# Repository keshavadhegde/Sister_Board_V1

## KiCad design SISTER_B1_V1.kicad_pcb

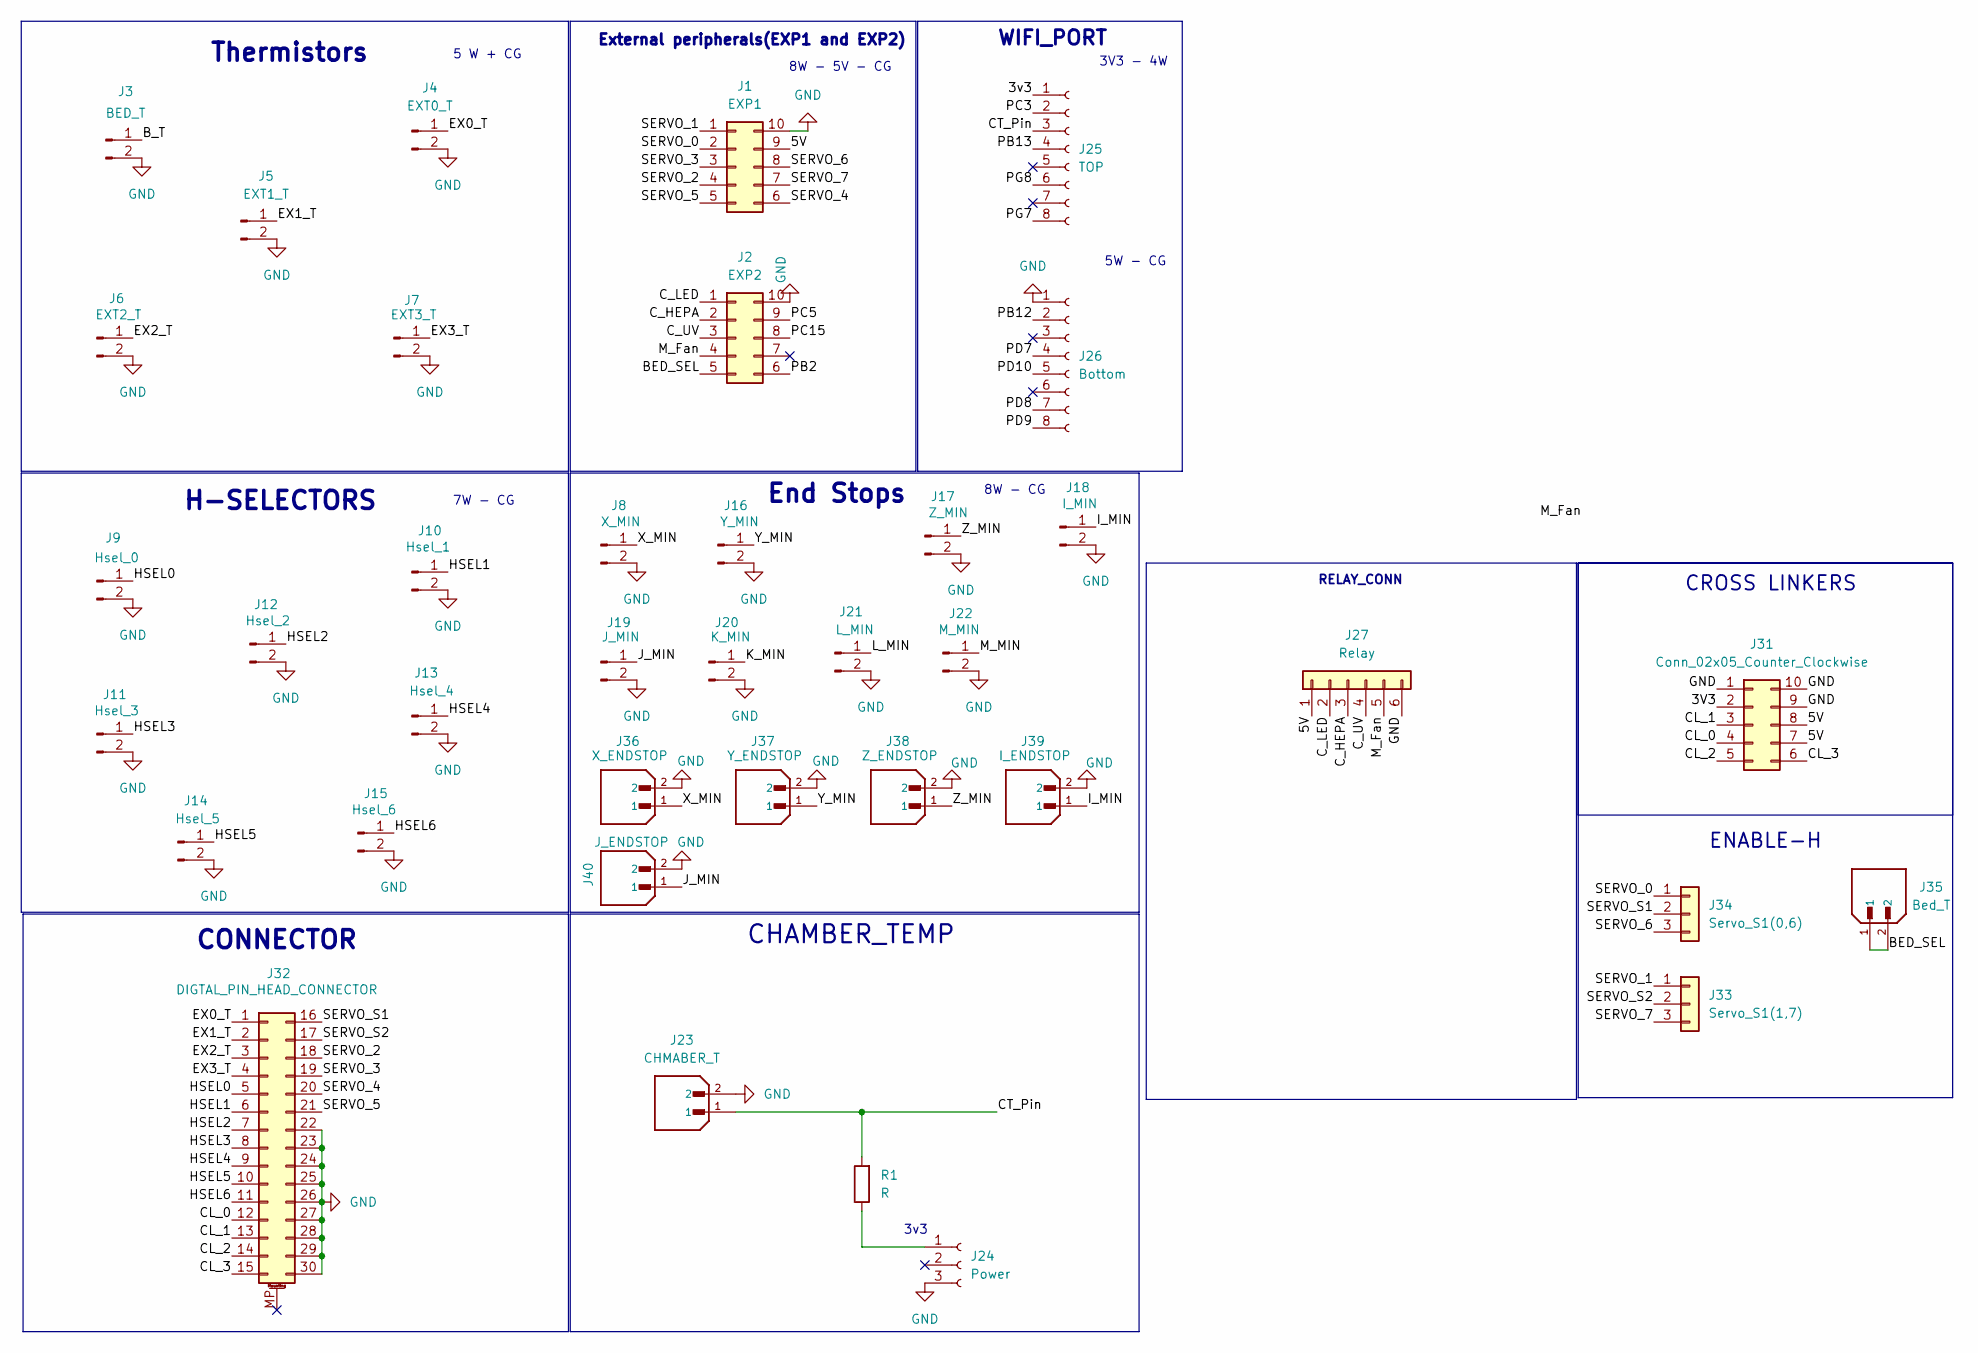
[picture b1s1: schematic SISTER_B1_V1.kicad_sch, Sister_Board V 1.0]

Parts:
J1: EXP1; PinSocket_2x05_P2.54mm_Vertical_SMD
J2: EXP2; PinSocket_2x05_P2.54mm_Vertical_SMD
J3: BED_T; PinSocket_1x02_P2.54mm_Vertical_SMD_Pin1Left
J4: EXT0_T; PinSocket_1x02_P2.54mm_Vertical_SMD_Pin1Left
J5: EXT1_T; PinSocket_1x02_P2.54mm_Vertical_SMD_Pin1Left
J6: EXT2_T; PinSocket_1x02_P2.54mm_Vertical_SMD_Pin1Left
J7: EXT3_T; PinSocket_1x02_P2.54mm_Vertical_SMD_Pin1Left
J8: X_MIN; PinSocket_1x02_P2.54mm_Vertical_SMD_Pin1Left
J9: Hsel_0; PinSocket_1x02_P2.54mm_Vertical_SMD_Pin1Left
J10: Hsel_1; PinSocket_1x02_P2.54mm_Vertical_SMD_Pin1Left
J11: Hsel_3; PinSocket_1x02_P2.54mm_Vertical_SMD_Pin1Left
J12: Hsel_2; PinSocket_1x02_P2.54mm_Vertical_SMD_Pin1Left
J13: Hsel_4; PinSocket_1x02_P2.54mm_Vertical_SMD_Pin1Left
J14: Hsel_5; PinSocket_1x02_P2.54mm_Vertical_SMD_Pin1Left
J15: Hsel_6; PinSocket_1x02_P2.54mm_Vertical_SMD_Pin1Left
J16: Y_MIN; PinSocket_1x02_P2.54mm_Vertical_SMD_Pin1Left
J17: Z_MIN; PinSocket_1x02_P2.54mm_Vertical_SMD_Pin1Left
J18: I_MIN; PinSocket_1x02_P2.54mm_Vertical_SMD_Pin1Left
J19: J_MIN; PinSocket_1x02_P2.54mm_Vertical_SMD_Pin1Left
J20: K_MIN; PinSocket_1x02_P2.54mm_Vertical_SMD_Pin1Left
J21: L_MIN; PinSocket_1x02_P2.54mm_Vertical_SMD_Pin1Left
J22: M_MIN; PinSocket_1x02_P2.54mm_Vertical_SMD_Pin1Left
J23: CHMABER_T; PinSocket_1x02_P2.54mm_Vertical_SMD_Pin1Left; PARTREV N/A
J24: Power; PinHeader_1x03_P2.54mm_Vertical_SMD_Pin1Left
J25: TOP; PinHeader_1x08_P2.54mm_Vertical_SMD_Pin1Left
J26: Bottom; PinHeader_1x08_P2.54mm_Vertical_SMD_Pin1Left
J27: Relay; PinHeader_1x06_P2.54mm_Vertical
J31: Conn_02x05_Counter_Clockwise; PinSocket_2x05_P2.54mm_Vertical_SMD
J32: DIGTAL_PIN_HEAD_CONNECTOR; IDC-Header_2x15-1MP_P2.54mm_Latch_Vertical
J33: Servo_S1(1,7); PinHeader_1x03_P2.54mm_Vertical
J34: Servo_S1(0,6); PinHeader_1x03_P2.54mm_Vertical
J35: Bed_T; PinSocket_1x02_P2.54mm_Vertical_SMD_Pin1Left; PARTREV N/A
J36: X_ENDSTOP; PinSocket_1x02_P2.54mm_Vertical_SMD_Pin1Left; PARTREV N/A
J37: Y_ENDSTOP; PinSocket_1x02_P2.54mm_Vertical_SMD_Pin1Left; PARTREV N/A
J38: Z_ENDSTOP; PinSocket_1x02_P2.54mm_Vertical_SMD_Pin1Left; PARTREV N/A
J39: I_ENDSTOP; PinSocket_1x02_P2.54mm_Vertical_SMD_Pin1Left; PARTREV N/A
J40: J_ENDSTOP; PinSocket_1x02_P2.54mm_Vertical_SMD_Pin1Left; PARTREV N/A
R1: R; R_Axial_DIN0207_L6.3mm_D2.5mm_P7.62mm_Horizontal

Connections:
/3V3: J31.2
/3v3: J25.1
/5V: J1.9, J27.1, J31.7, J31.8
/BED_SEL: J2.5, J35.1, J35.2
/B_T: J3.1
/CL_0: J31.4, J32.12
/CL_1: J31.3, J32.13
/CL_2: J31.5, J32.14
/CL_3: J31.6, J32.15
/CT_Pin: J23.1, J25.3, R1.2
/C_HEPA: J2.2, J27.3
/C_LED: J2.1, J27.2
/C_UV: J2.3, J27.4
/EX0_T: J4.1, J32.1
/EX1_T: J5.1, J32.2
/EX2_T: J6.1, J32.3
/EX3_T: J7.1, J32.4
/HSEL0: J9.1, J32.5
/HSEL1: J10.1, J32.6
/HSEL2: J12.1, J32.7
/HSEL3: J11.1, J32.8
/HSEL4: J13.1, J32.9
/HSEL5: J14.1, J32.10
/HSEL6: J15.1, J32.11
/I_MIN: J18.1, J39.1
/J_MIN: J19.1, J40.1
/K_MIN: J20.1
/L_MIN: J21.1
/M_Fan: J2.4, J27.5
/M_MIN: J22.1
/PB2: J2.6
/PB12: J26.2
/PB13: J25.4
/PC3: J25.2
/PC5: J2.9
/PC15: J2.8
/PD7: J26.4
/PD8: J26.7
/PD9: J26.8
/PD10: J26.5
/PG7: J25.8
/PG8: J25.6
/SERVO_0: J1.2, J34.1
/SERVO_1: J1.1, J33.1
/SERVO_2: J1.4, J32.18
/SERVO_3: J1.3, J32.19
/SERVO_4: J1.6, J32.20
/SERVO_5: J1.5, J32.21
/SERVO_6: J1.8, J34.3
/SERVO_7: J1.7, J33.3
/SERVO_S1: J32.16, J34.2
/SERVO_S2: J32.17, J33.2
/X_MIN: J8.1, J36.1
/Y_MIN: J16.1, J37.1
/Z_MIN: J17.1, J38.1
GND: J1.10, J2.10, J3.2, J4.2, J5.2, J6.2, J7.2, J8.2, J9.2, J10.2, J11.2, J12.2, J13.2, J14.2, J15.2, J16.2, J17.2, J18.2, J19.2, J20.2, J21.2, J22.2, J23.2, J24.3, J26.1, J27.6, J31.1, J31.9, J31.10, J32.22, J32.23, J32.24, J32.25, J32.26, J32.27, J32.28, J32.29, J32.30, J36.2, J37.2, J38.2, J39.2, J40.2
unnamed: J24.1, R1.1

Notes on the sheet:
7W - CG
5 W + CG
Thermistors
ENABLE-H
8W - CG
H-SELECTORS
External peripherals(EXP1 and EXP2)
CONNECTOR
3v3
5W - CG
CROSS LINKERS
3V3 - 4W
RELAY_CONN
8W - 5V - CG
End Stops
CHAMBER_TEMP
WIFI_PORT

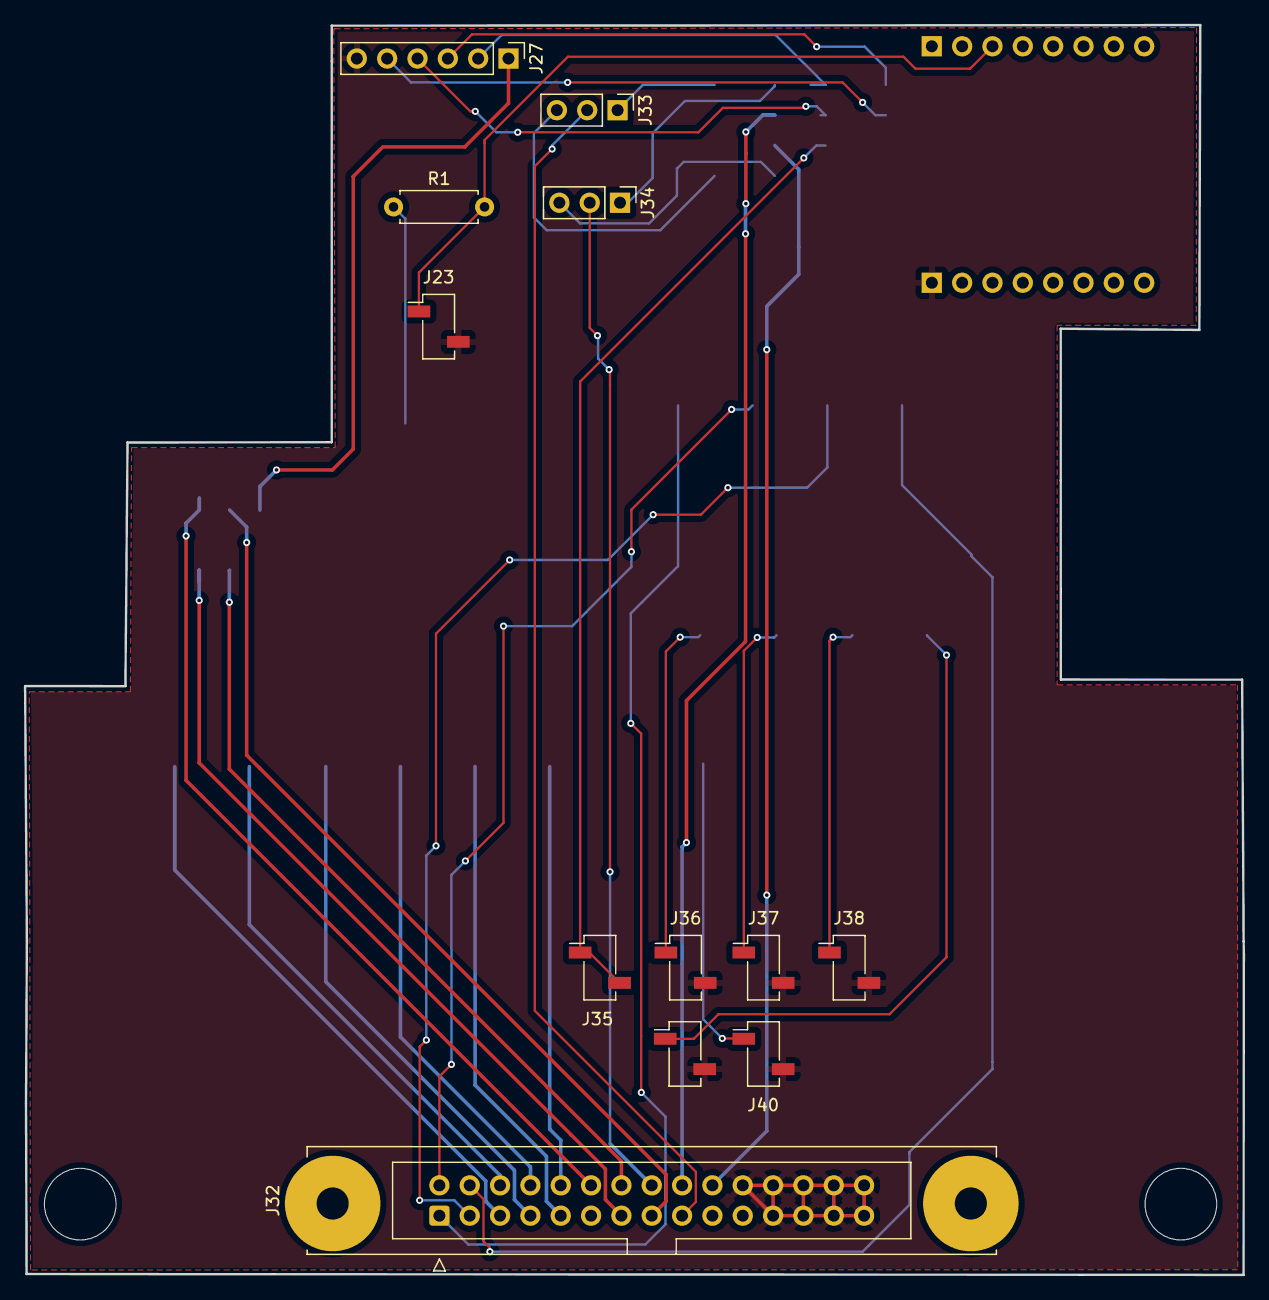
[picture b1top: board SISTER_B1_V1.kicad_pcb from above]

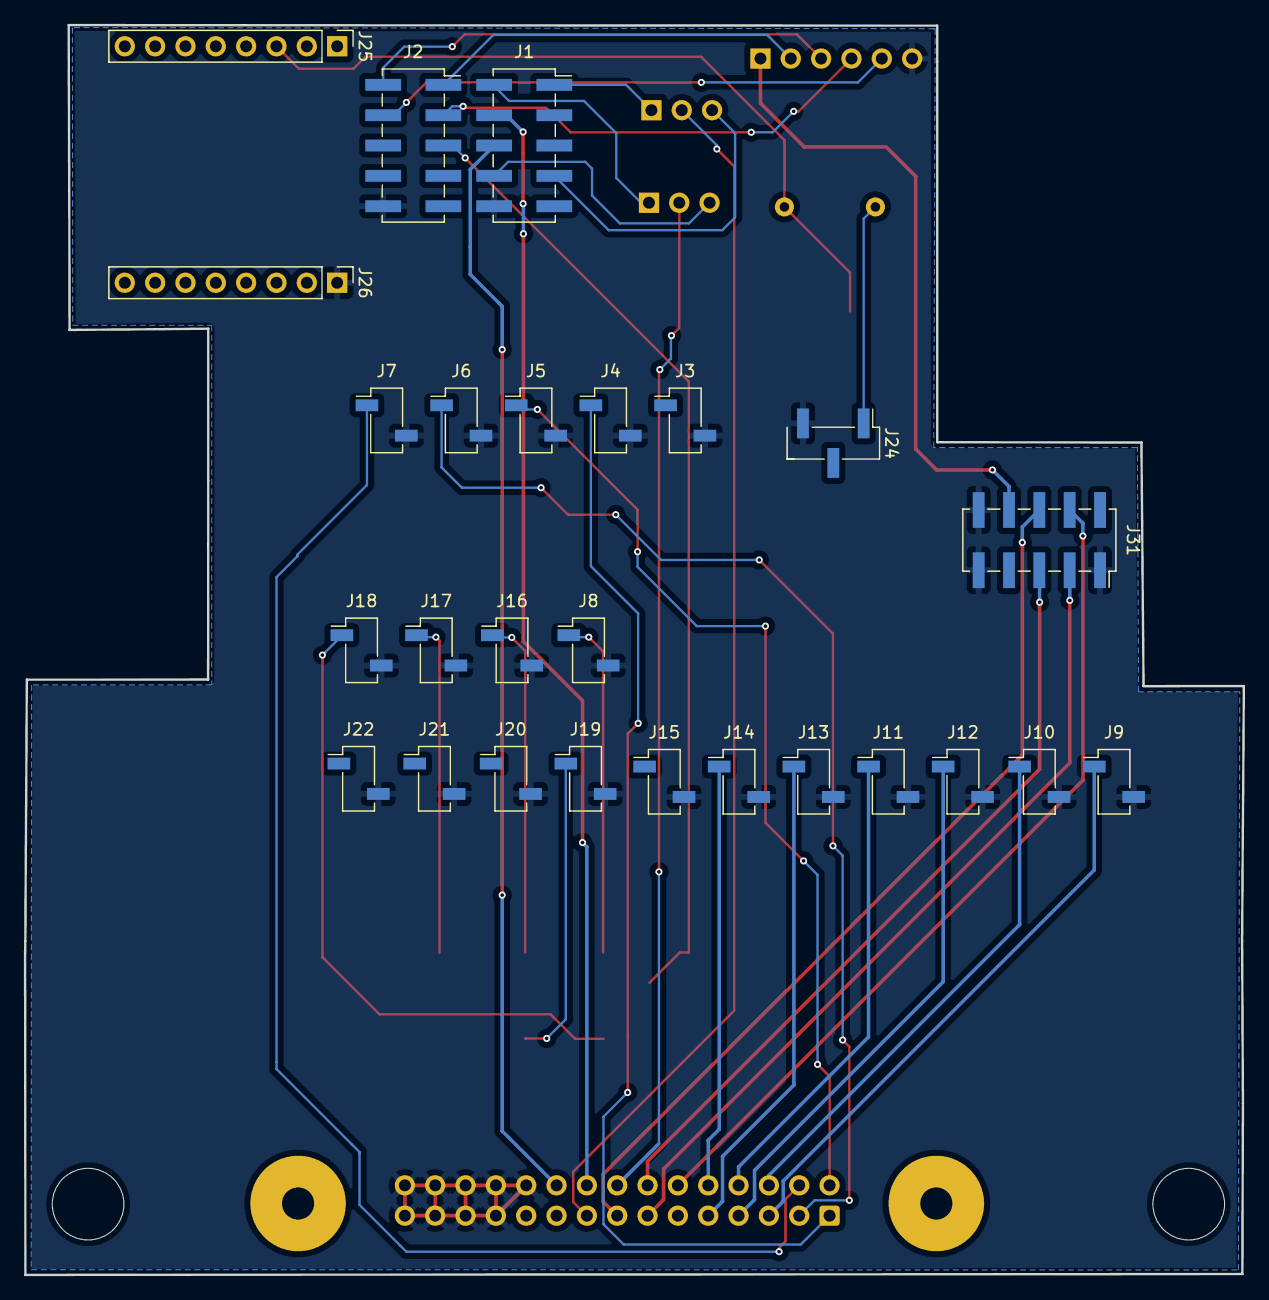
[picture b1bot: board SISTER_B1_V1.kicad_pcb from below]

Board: 2 copper layers, 102.1 x 104.7 mm, 38 parts (26 on the bottom side), 39 nets.

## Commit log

2025-01-08 [Keshav add part]
